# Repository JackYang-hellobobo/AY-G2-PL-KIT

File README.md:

# AY-G2-PL-KIT

### ***MSP430口袋实验套件AY-G2PL KIT***

1、[MSP430口袋实验套件AY-G2PL KIT 官方地址](http://www.hpati.com/ay_scm_pack/product_33.html)  

2、[德州仪器 TI MSP430G2553 资料详情网址](https://www.ti.com.cn/product/cn/MSP430G2553)  

3、[MSP430G2553 LaunchPad™ Development Kit(MSP
‑‑EXP430G2ET)](https://www.ti.com/lit/ug/slau772a/slau772a.pdf?ts=1737384075369)  

4、[
MSP-EXP430G2ET
MSP430™ LaunchPad™ development kit for value line MCU
](https://www.ti.com/tool/MSP-EXP430G2ET)

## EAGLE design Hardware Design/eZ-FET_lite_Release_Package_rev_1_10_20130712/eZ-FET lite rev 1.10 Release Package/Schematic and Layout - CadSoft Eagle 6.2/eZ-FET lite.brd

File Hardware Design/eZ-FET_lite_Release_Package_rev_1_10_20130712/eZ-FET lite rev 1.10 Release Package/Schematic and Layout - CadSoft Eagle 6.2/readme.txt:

Please download the MSP430 schematic symbols and footprints library for use with the Eagle CAD tool (Rev. E) from http://www.ti.com/litv/zip/slac060e
Please note that the Eagle library package CSTCR6M used for component Q101 does not include tCream layer. It should be added manually before submitting data to production.

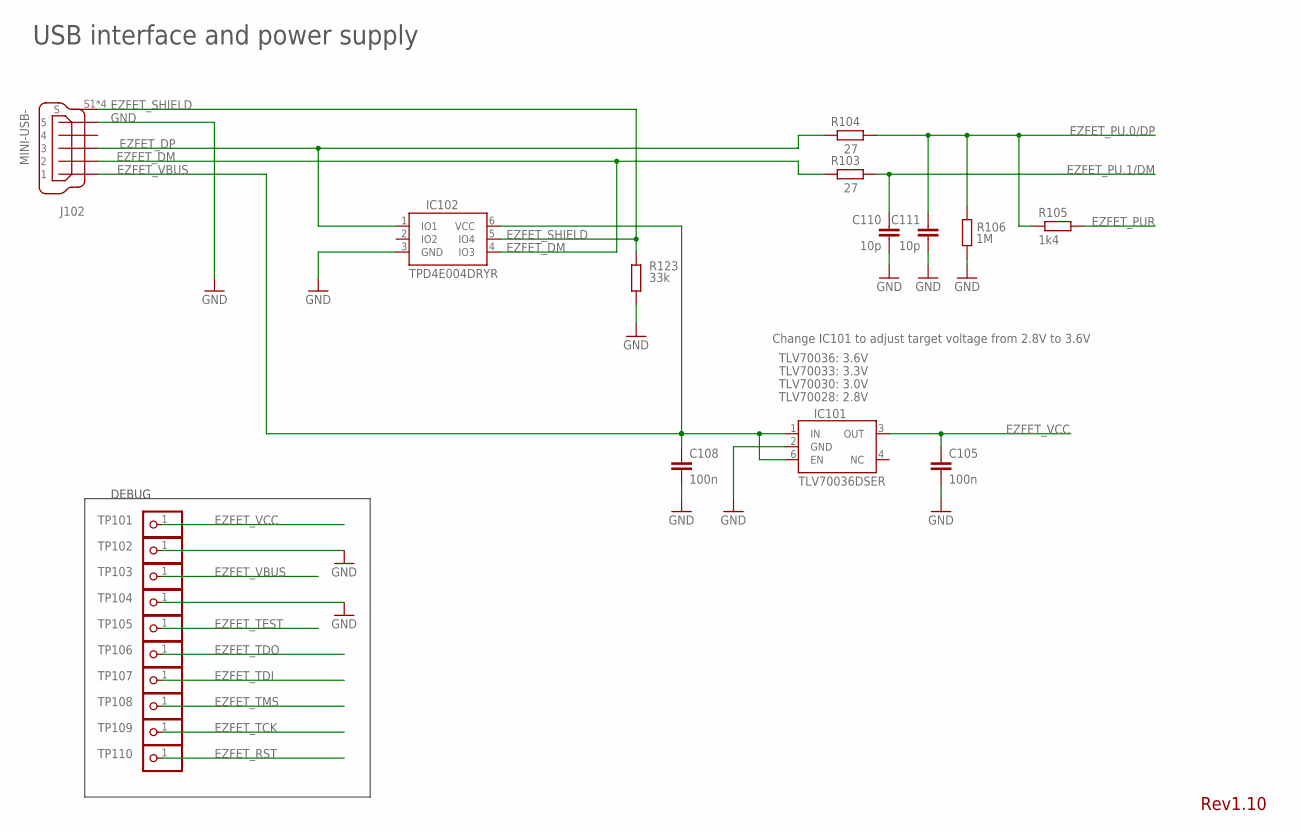
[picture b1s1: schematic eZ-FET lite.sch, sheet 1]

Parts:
C105, C108: 100n; C0402
C110, C111: 10p; C0402
IC101: TLV70036DSER; SON(DRY)6
IC102: TPD4E004DRYR; SON(DRY)6
J102: MINI-USB-; UX62M-B-5P
R103, R104: 27; R0402
R105: 1k4; R0402
R106: 1M; R0402
R123: 33k; R0402
TP101, TP102, TP103, TP104, TP105, TP106, TP107, TP108, TP109, TP110: TEST_PIN2; 1X01

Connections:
EZFET_DM: IC102.4 (IO3), J102.2, R103.1
EZFET_DP: IC102.1 (IO1), J102.3, R104.1
EZFET_PU.0/DP: C111.1, R104.2, R105.1, R106.1; also elsewhere on the board
EZFET_PU.1/DM: C110.1, R103.2; also elsewhere on the board
EZFET_PUR: R105.2; also elsewhere on the board
EZFET_RST: TP110.1; also elsewhere on the board
EZFET_SHIELD: IC102.5 (IO4), J102.S1 (S), J102.S2 (S), J102.S3 (S), J102.S4 (S), R123.1
EZFET_TCK: TP109.1; also elsewhere on the board
EZFET_TDI: TP107.1; also elsewhere on the board
EZFET_TDO: TP106.1; also elsewhere on the board
EZFET_TEST: TP105.1; also elsewhere on the board
EZFET_TMS: TP108.1; also elsewhere on the board
EZFET_VBUS: C108.1, IC101.1 (IN), IC101.6 (EN), IC102.6 (VCC), J102.1, TP103.1; also elsewhere on the board
EZFET_VCC: C105.1, IC101.3 (OUT), TP101.1; also elsewhere on the board
GND: C105.2, C108.2, C110.2, C111.2, IC101.2 (GND), IC102.3 (GND), J102.5, R106.2, R123.2, TP102.1, TP104.1; also elsewhere on the board

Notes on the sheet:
USB interface and power supply
DEBUG
Rev1.10
Change IC101 to adjust target voltage from 2.8V to 3.6V
TLV70036: 3.6V
TLV70033: 3.3V
TLV70030: 3.0V
TLV70028: 2.8V

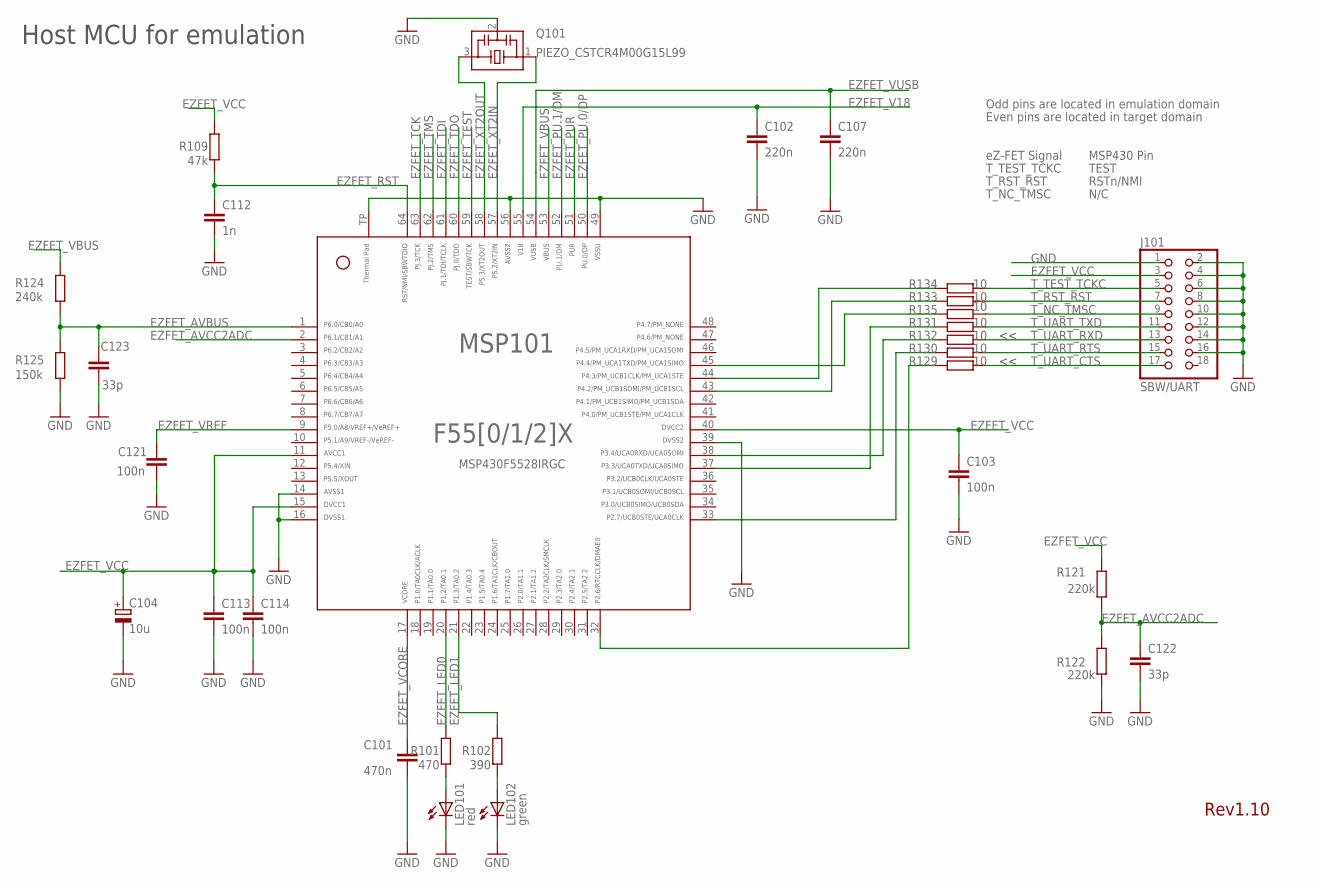
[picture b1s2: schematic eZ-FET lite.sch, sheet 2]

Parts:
C101: 470n; C0402
C102, C107: 220n; C0402
C103, C113, C114, C121: 100n; C0402
C104: 10u; A/3216-18R
C112: 1n; C0402
C122, C123: 33p; C0402
J101: SBW/UART; 2X09
LED101: red; CHIP-LED0603
LED102: green; CHIP-LED0603
MSP101: MSP430F5528IRGC; RGC64
Q101: PIEZO_CSTCR4M00G15L99; CSTCR6M
R101: 470; R0402
R102: 390; R0402
R109: 47k; R0402
R121, R122: 220k; R0402
R124: 240k; R0402
R125: 150k; R0402
R129, R130, R131, R132, R133, R134, R135: 10; R0402

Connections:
EZFET_AVBUS: C123.2, MSP101.1, R124.2, R125.1
EZFET_AVCC2ADC: C122.2, MSP101.2, R121.2, R122.1
EZFET_LED0: MSP101.20, R101.2
EZFET_LED1: MSP101.21, R102.2
EZFET_PU.0/DP: MSP101.50; also elsewhere on the board
EZFET_PU.1/DM: MSP101.52; also elsewhere on the board
EZFET_PUR: MSP101.51; also elsewhere on the board
EZFET_RST: C112.1, MSP101.64, R109.1; also elsewhere on the board
EZFET_SBWTCK: MSP101.44, R134.2
EZFET_SBWTDIO: MSP101.43, R133.2
EZFET_TCK: MSP101.63; also elsewhere on the board
EZFET_TDI: MSP101.61; also elsewhere on the board
EZFET_TDO: MSP101.60; also elsewhere on the board
EZFET_TEST: MSP101.59; also elsewhere on the board
EZFET_TMS: MSP101.62; also elsewhere on the board
EZFET_UARTCTS: MSP101.32, R129.2
EZFET_UARTRTS: MSP101.33, R130.2
EZFET_UARTRXD: MSP101.38, R132.2
EZFET_UARTTXD: MSP101.37, R131.2
EZFET_V18: C102.1, MSP101.55
EZFET_VBUS: MSP101.53, R124.1; also elsewhere on the board
EZFET_VCC: C103.1, C104.+, C113.1, C114.1, J101.3, MSP101.11, MSP101.15, MSP101.40, R109.2, R121.1; also elsewhere on the board
EZFET_VCORE: C101.1, MSP101.17
EZFET_VREF: C121.1, MSP101.9
EZFET_VUSB: C107.1, MSP101.54
EZFET_XT2IN: MSP101.57, Q101.1
EZFET_XT2OUT: MSP101.58, Q101.3
GND: C101.2, C102.2, C103.2, C104.-, C107.2, C112.2, C113.2, C114.2, C121.2, C122.1, C123.1, J101.1, J101.2, J101.4, J101.6, J101.8, J101.10, J101.12, J101.14, J101.16, LED101.C, LED102.C, MSP101.14, MSP101.16, MSP101.39, MSP101.49, MSP101.56, MSP101.TP, Q101.2, R122.2, R125.2; also elsewhere on the board
unnamed: LED101.A, R101.1
unnamed: LED102.A, R102.1
unnamed: MSP101.45, R135.2
T_NC_TMSC: J101.9, R135.1
T_RST_RST: J101.7, R133.1
T_TEST_TCKC: J101.5, R134.1
T_UART_CTS: J101.17, R129.1
T_UART_RTS: J101.15, R130.1
T_UART_RXD: J101.13, R132.1
T_UART_TXD: J101.11, R131.1

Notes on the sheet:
Host MCU for emulation
MSP430F5528IRGC
Rev1.10
Odd pins are located in emulation domain
Even pins are located in target domain
eZ-FET Signal
T_TEST_TCKC
T_RST_RST
T_NC_TMSC
MSP430 Pin
TEST
RSTn/NMI
N/C

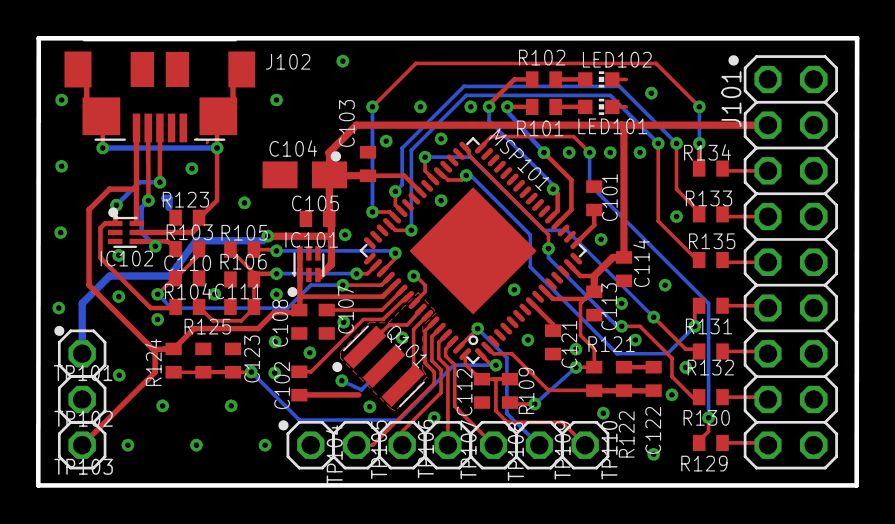
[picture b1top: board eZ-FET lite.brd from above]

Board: 2 copper layers, 45.5 x 24.8 mm, 52 parts (0 on the bottom side), 41 nets.

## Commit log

2025-01-21 init release
2025-01-21 Upload BOM
2025-01-21 Upload PDF
2025-01-22 Upload driverlib
2025-01-22 New PrjTemple For CCS12.81
2025-01-22 driverlib_v0.1
2025-01-23 Upload G2553 Resources
2025-01-24 Upload F5529LP_LaunchBOM.xls
2025-01-24 Upload G2ET HD
2025-01-24 Upload eZ-FET_lite Emulation Probe
2025-01-24 [ImgBot] Optimize images
    /G2553/LaunchPadMSP430G2452-v1.5.jpg -- 482.66kb -> 423.74kb (12.21%)
2025-01-26 Upload HT1621B LCD DriverChip Datasheet
